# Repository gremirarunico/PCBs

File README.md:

# PCBs
## Informazioni
Repository privato per backup & share di PCB realizzati con KiCAD

## KiCad version
7.0.8

## License
Very easy to understand:
All the Hardware in this repository is under CERN-OHL-S v2
All the Software is under GPLv3
All the documentation is under CC-BY-SA 4.0

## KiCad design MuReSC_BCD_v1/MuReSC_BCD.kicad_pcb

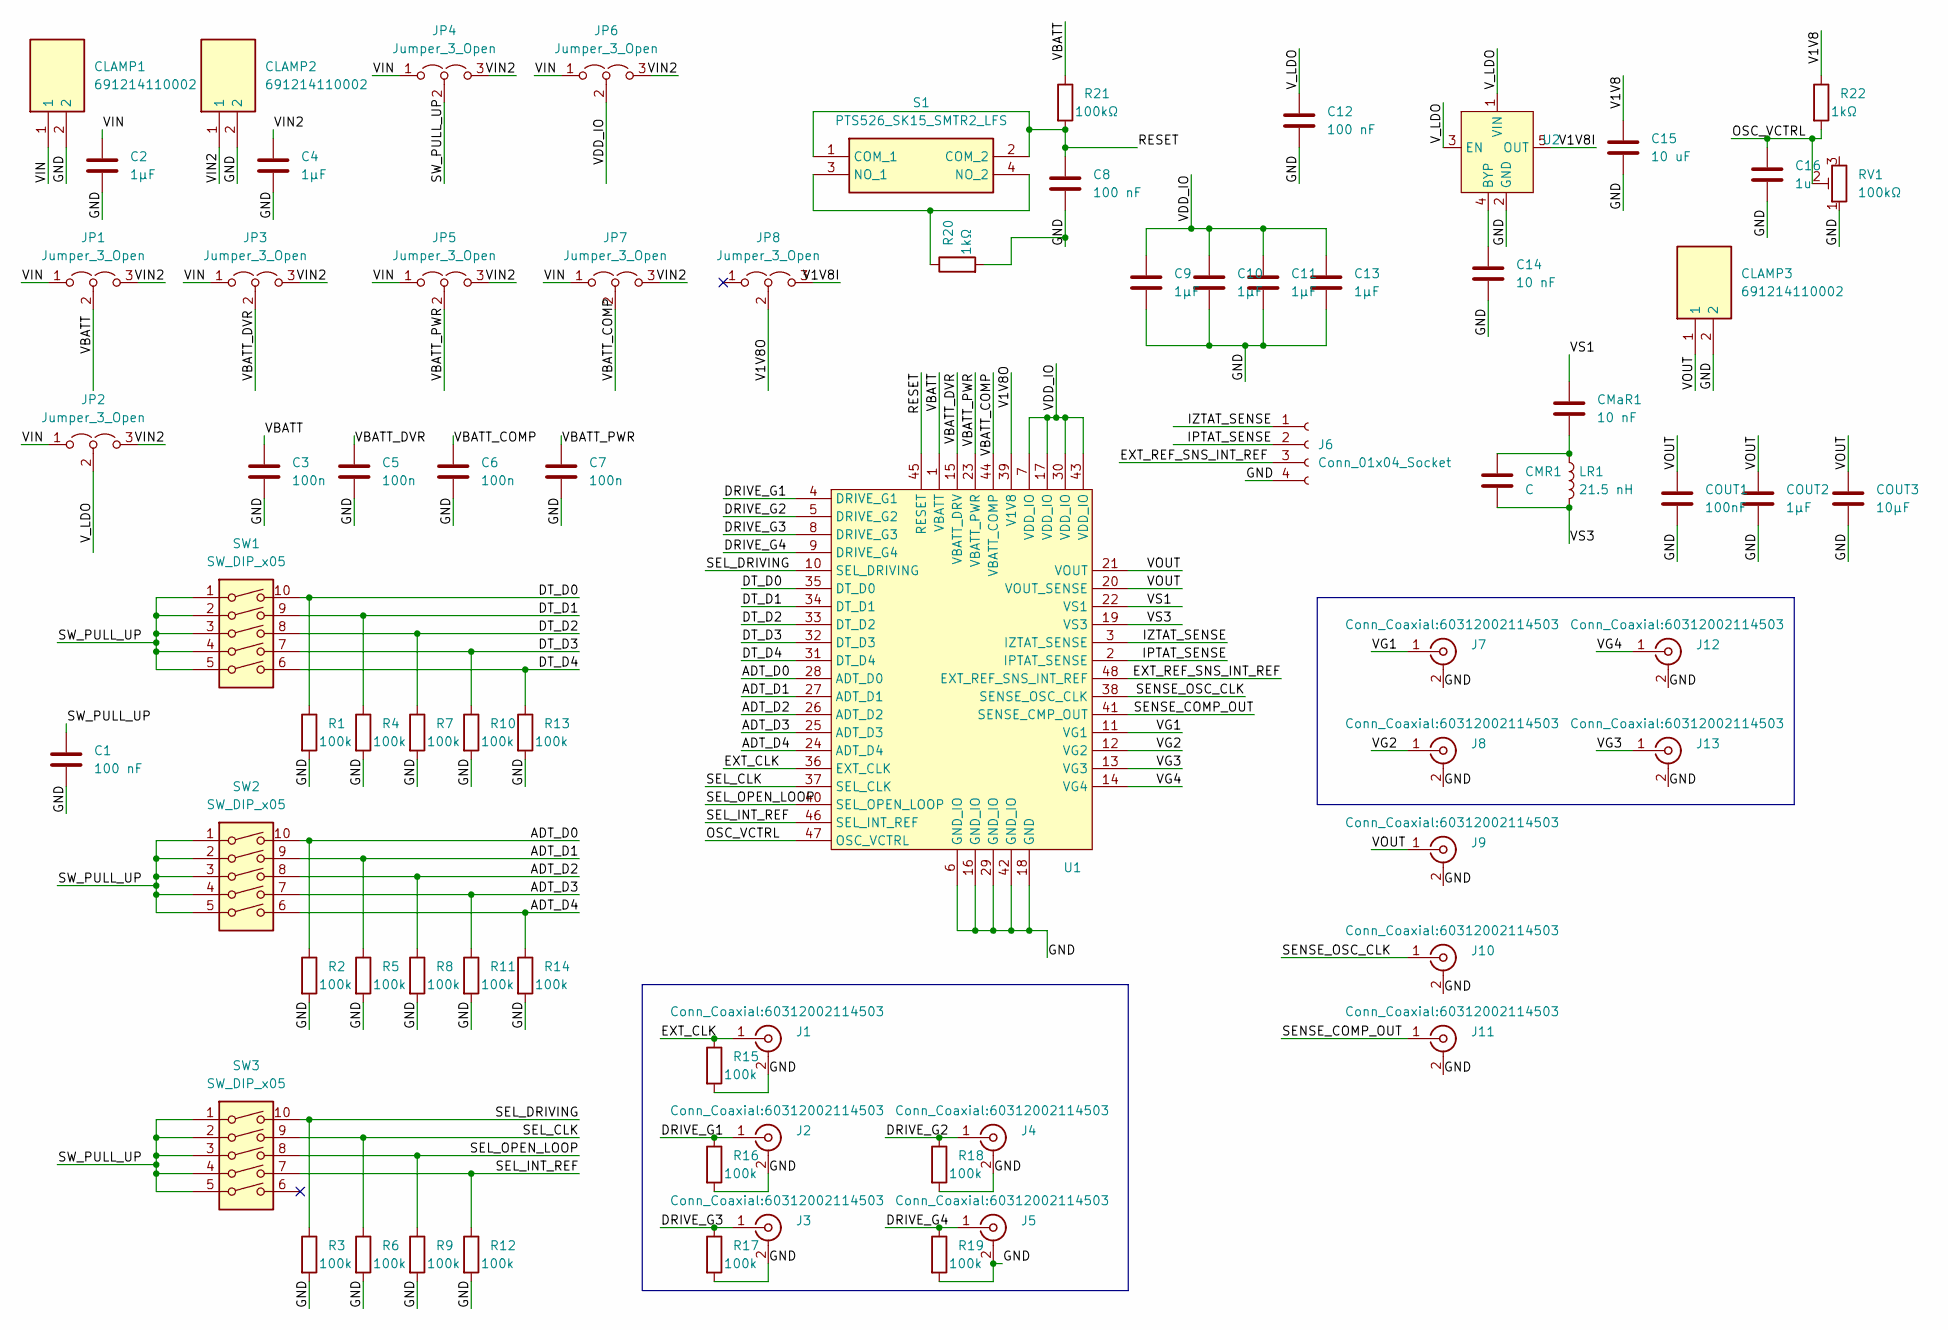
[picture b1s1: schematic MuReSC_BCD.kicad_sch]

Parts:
C1, C8, C12: 100 nF; C_0603_1608Metric_Pad1.08x0.95mm_HandSolder
C2, C4, C9, C10, C11, C13: 1µF; C_0603_1608Metric_Pad1.08x0.95mm_HandSolder
C3, C5, C6, C7: 100n; C_0603_1608Metric_Pad1.08x0.95mm_HandSolder
C14: 10 nF; C_0603_1608Metric_Pad1.08x0.95mm_HandSolder
C15: 10 uF; C_0603_1608Metric_Pad1.08x0.95mm_HandSolder
C16: 1u; C_0603_1608Metric_Pad1.08x0.95mm_HandSolder
CLAMP1, CLAMP2, CLAMP3: 691214110002; Mouser Part Number 710-691214110002
CMR1: C; C_0603_1608Metric_Pad1.08x0.95mm_HandSolder
CMaR1: 10 nF; C_0603_1608Metric_Pad1.08x0.95mm_HandSolder
COUT1: 100nF; C_0603_1608Metric_Pad1.08x0.95mm_HandSolder
COUT2: 1µF; C_0603_1608Metric_Pad1.08x0.95mm_HandSolder
COUT3: 10µF; C_0603_1608Metric_Pad1.08x0.95mm_HandSolder
J1, J2, J3, J4, J5, J7, J8, J9, J10, J11, J12, J13: Conn_Coaxial:60312002114503; SMA_Wurth_60312002114503_Vertical
J6: Conn_01x04_Socket; PinHeader_1x04_P2.54mm_Vertical
JP1, JP2, JP3, JP4, JP5, JP6, JP7, JP8: Jumper_3_Open; PinHeader_1x03_P2.54mm_Vertical
LR1: 21.5 nH; Coilcraft-Square-Air-Core-Inductors-all
R1, R2, R3, R4, R5, R6, R7, R8, R9, R10, R11, R12, R13, R14, R15, R16, R17, R18, R19: 100k; R_0603_1608Metric_Pad0.98x0.95mm_HandSolder
R20, R22: 1kΩ; R_0603_1608Metric_Pad0.98x0.95mm_HandSolder
R21: 100kΩ; R_0603_1608Metric_Pad0.98x0.95mm_HandSolder
RV1: 100kΩ; TS63X-VISHAY
S1: PTS526_SK15_SMTR2_LFS; PTS526SK15SMTR2LFS; Mouser Part Number 611-PTS526SK15SMR2L
SW1, SW2, SW3: SW_DIP_x05; DIP-10_W10.16mm_LongPads
U1: TQFP-48_7x7mm_P0.5mm
U2: SOT-23-5_HandSoldering

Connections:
/ADT_D0: R2.1, SW2.10, U1.28 (ADT_D0)
/ADT_D1: R5.1, SW2.9, U1.27 (ADT_D1)
/ADT_D2: R8.1, SW2.8, U1.26 (ADT_D2)
/ADT_D3: R11.1, SW2.7, U1.25 (ADT_D3)
/ADT_D4: R14.1, SW2.6, U1.24 (ADT_D4)
/DRIVE_G1: J2.1 (In), R16.1, U1.4 (DRIVE_G1)
/DRIVE_G2: J4.1 (In), R18.1, U1.5 (DRIVE_G2)
/DRIVE_G3: J3.1 (In), R17.1, U1.8 (DRIVE_G3)
/DRIVE_G4: J5.1 (In), R19.1, U1.9 (DRIVE_G4)
/DT_D0: R1.1, SW1.10, U1.35 (DT_D0)
/DT_D1: R4.1, SW1.9, U1.34 (DT_D1)
/DT_D2: R7.1, SW1.8, U1.33 (DT_D2)
/DT_D3: R10.1, SW1.7, U1.32 (DT_D3)
/DT_D4: R13.1, SW1.6, U1.31 (DT_D4)
/EXT_CLK: J1.1 (In), R15.1, U1.36 (EXT_CLK)
/EXT_REF_SNS_INT_REF: J6.3, U1.48 (EXT_REF_SNS_INT_REF)
/GND: C1.2, C2.2, C3.2, C4.2, C5.2, C6.2, C7.2, C8.2, C9.2, C10.2, C11.2, C12.2, C13.2, C14.2, C15.2, C16.2, CLAMP1.2, CLAMP2.2, CLAMP3.2, COUT1.2, COUT2.2, COUT3.2, J1.2 (Ext), J2.2 (Ext), J3.2 (Ext), J4.2 (Ext), J5.2 (Ext), J6.4, J7.2 (Ext), J8.2 (Ext), J9.2 (Ext), J10.2 (Ext), J11.2 (Ext), J12.2 (Ext), J13.2 (Ext), R1.2, R2.2, R3.2, R4.2, R5.2, R6.2, R7.2, R8.2, R9.2, R10.2, R11.2, R12.2, R13.2, R14.2, R15.2, R16.2, R17.2, R18.2, R19.2, R20.2, RV1.1, U1.6 (GND_IO), U1.16 (GND_IO), U1.18 (GND), U1.29 (GND_IO), U1.42 (GND_IO), U2.2 (GND)
/IPTAT_SENSE: J6.2, U1.2 (IPTAT_SENSE)
/IZTAT_SENSE: J6.1, U1.3 (IZTAT_SENSE)
/OSC_VCTRL: C16.1, R22.2, RV1.2, U1.47 (OSC_VCTRL)
/RESET: C8.1, R21.2, S1.1 (COM_1), S1.2 (COM_2), U1.45 (RESET)
/SEL_CLK: R6.1, SW3.9, U1.37 (SEL_CLK)
/SEL_DRIVING: R3.1, SW3.10, U1.10 (SEL_DRIVING)
/SEL_INT_REF: R12.1, SW3.7, U1.46 (SEL_INT_REF)
/SEL_OPEN_LOOP: R9.1, SW3.8, U1.40 (SEL_OPEN_LOOP)
/SENSE_COMP_OUT: J11.1 (In), U1.41 (SENSE_CMP_OUT)
/SENSE_OSC_CLK: J10.1 (In), U1.38 (SENSE_OSC_CLK)
/SW_PULL_UP: C1.1, JP4.2 (C), SW1.1, SW1.2, SW1.3, SW1.4, SW1.5, SW2.1, SW2.2, SW2.3, SW2.4, SW2.5, SW3.1, SW3.2, SW3.3, SW3.4, SW3.5
/V1V8: C15.1, R22.1
/V1V8I: JP8.3 (B), U2.5 (OUT)
/V1V8O: JP8.2 (C), U1.39 (V1V8)
/VBATT: C3.1, JP1.2 (C), R21.1, U1.1 (VBATT)
/VBATT_COMP: C6.1, JP7.2 (C), U1.44 (VBATT_COMP)
/VBATT_DVR: C5.1, JP3.2 (C), U1.15 (VBATT_DRV)
/VBATT_PWR: C7.1, JP5.2 (C), U1.23 (VBATT_PWR)
/VDD_IO: C9.1, C10.1, C11.1, C13.1, JP6.2 (C), U1.7 (VDD_IO), U1.17 (VDD_IO), U1.30 (VDD_IO), U1.43 (VDD_IO)
/VG1: J7.1 (In), U1.11 (VG1)
/VG2: J8.1 (In), U1.12 (VG2)
/VG3: J13.1 (In), U1.13 (VG3)
/VG4: J12.1 (In), U1.14 (VG4)
/VIN: C2.1, CLAMP1.1, JP1.1 (A), JP2.1 (A), JP3.1 (A), JP4.1 (A), JP5.1 (A), JP6.1 (A), JP7.1 (A)
/VIN2: C4.1, CLAMP2.1, JP1.3 (B), JP2.3 (B), JP3.3 (B), JP4.3 (B), JP5.3 (B), JP6.3 (B), JP7.3 (B)
/VOUT: CLAMP3.1, COUT1.1, COUT2.1, COUT3.1, J9.1 (In), U1.20 (VOUT_SENSE), U1.21 (VOUT)
/VS1: CMaR1.1, U1.22 (VS1)
/VS3: CMR1.2, LR1.2, U1.19 (VS3)
/V_LDO: C12.1, JP2.2 (C), U2.1 (VIN), U2.3 (EN)
unnamed: CMR1.1, CMaR1.2, LR1.1
unnamed: R20.1, S1.3 (NO_1), S1.4 (NO_2)
unnamed: C14.1, U2.4 (BYP)

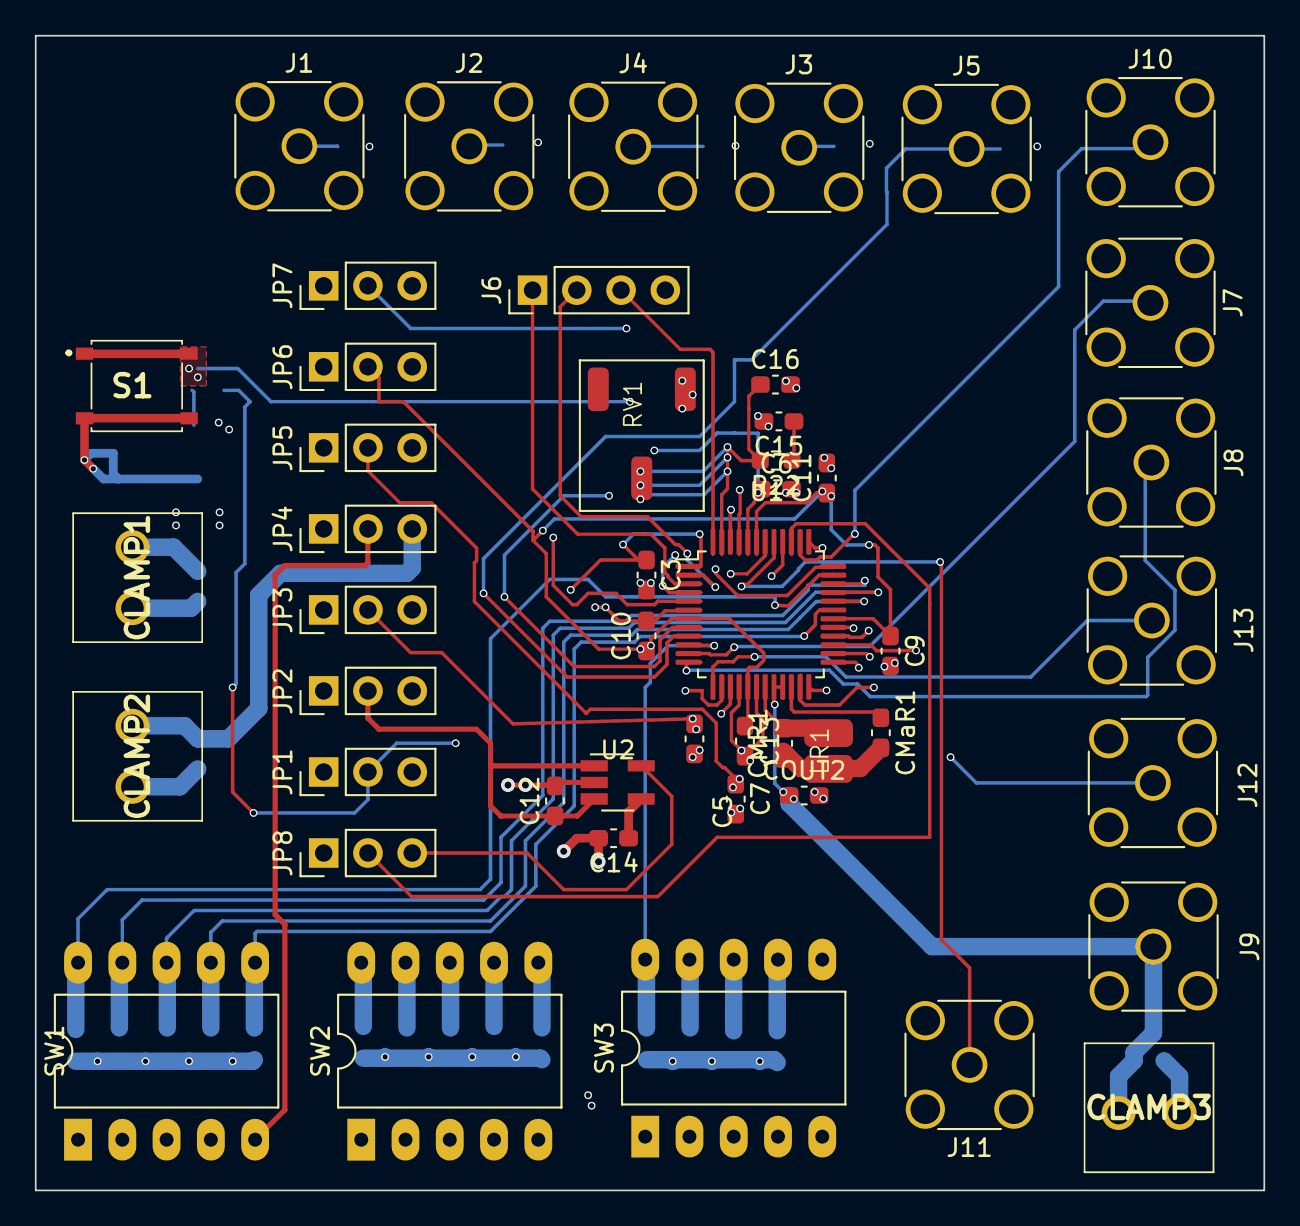
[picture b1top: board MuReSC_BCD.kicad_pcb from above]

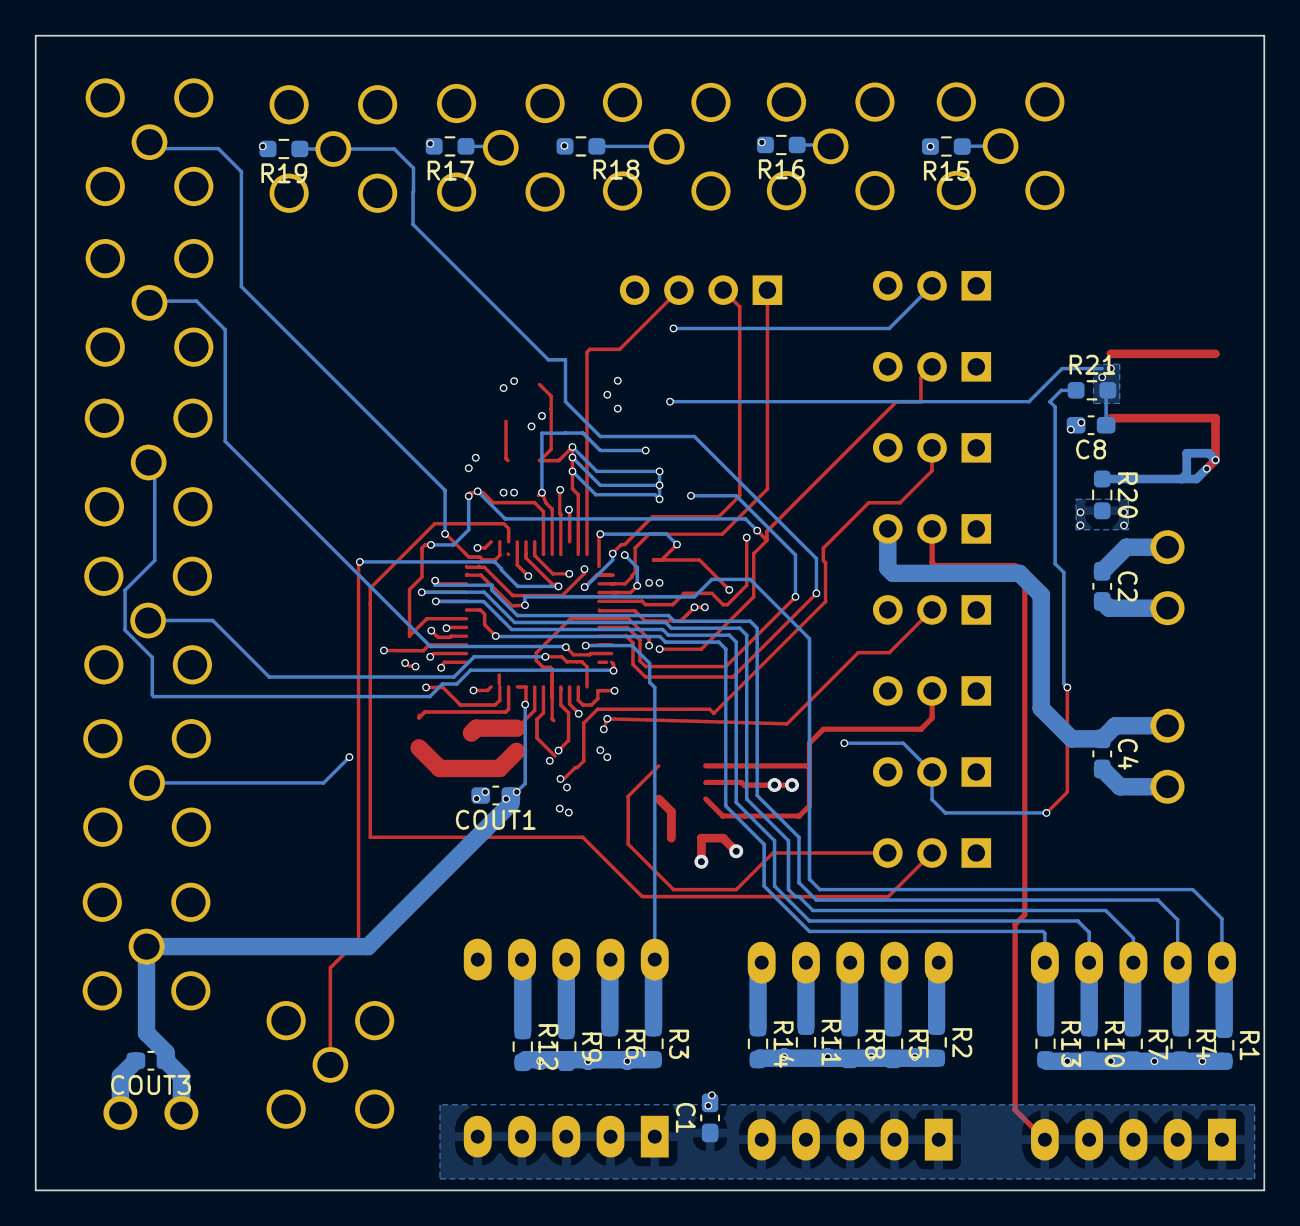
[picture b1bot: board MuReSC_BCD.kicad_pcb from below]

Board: 4 copper layers, 70.5 x 66.3 mm, 75 parts (27 on the bottom side), 49 nets.

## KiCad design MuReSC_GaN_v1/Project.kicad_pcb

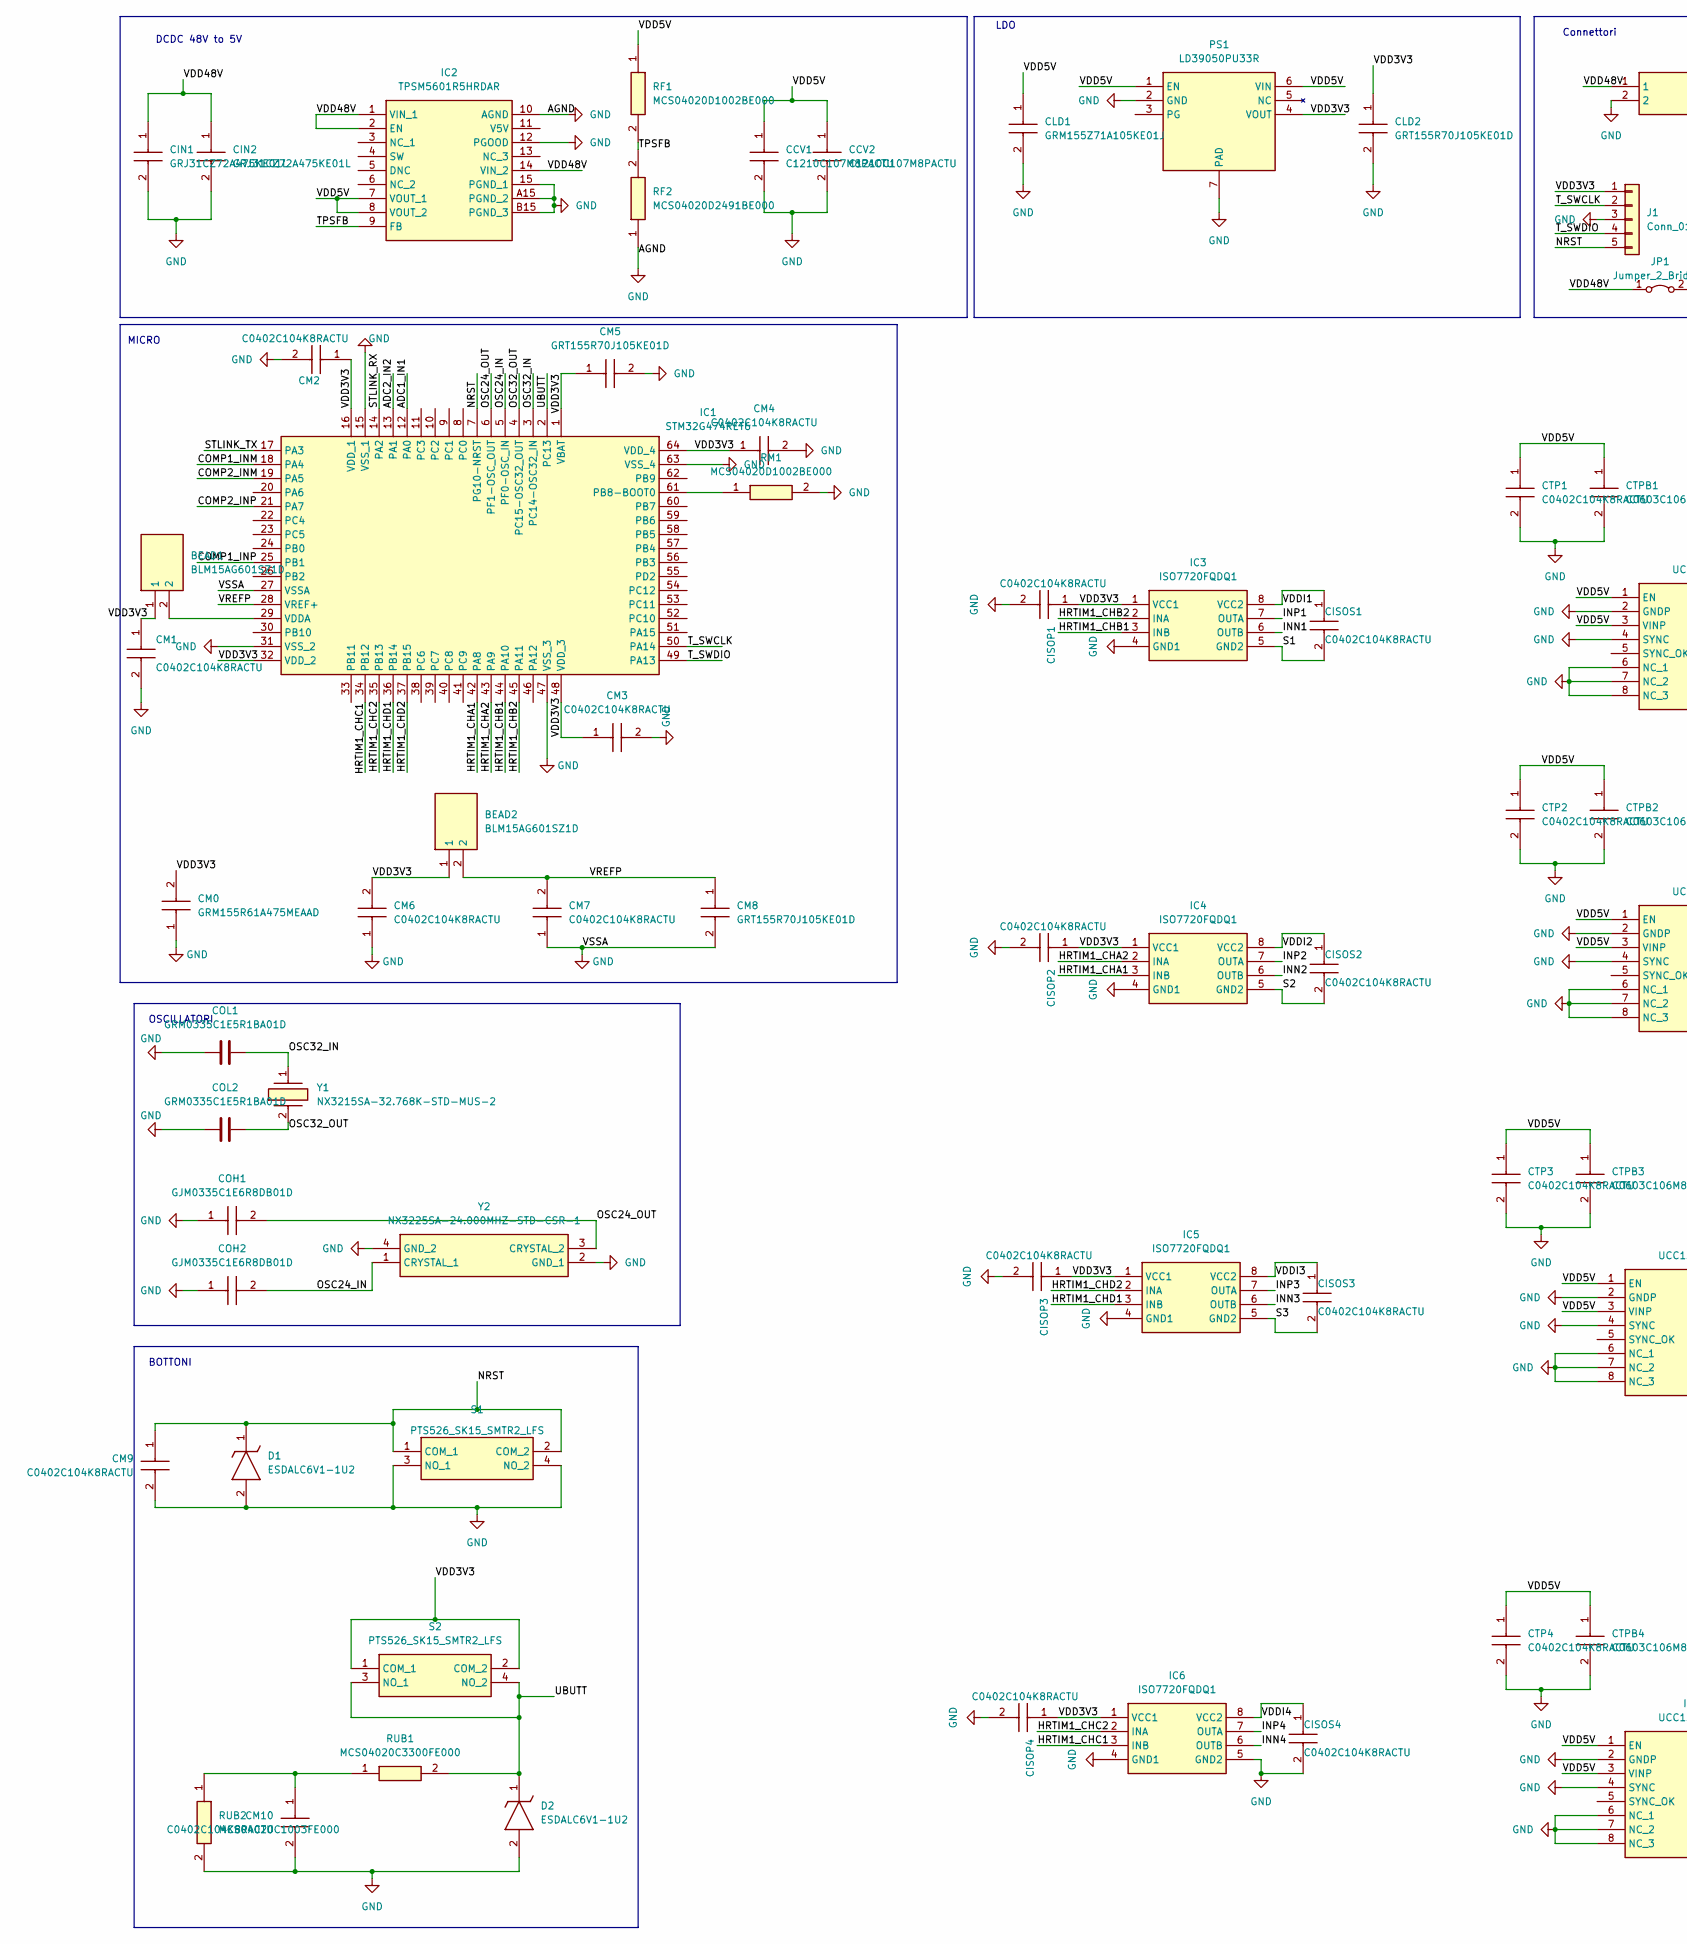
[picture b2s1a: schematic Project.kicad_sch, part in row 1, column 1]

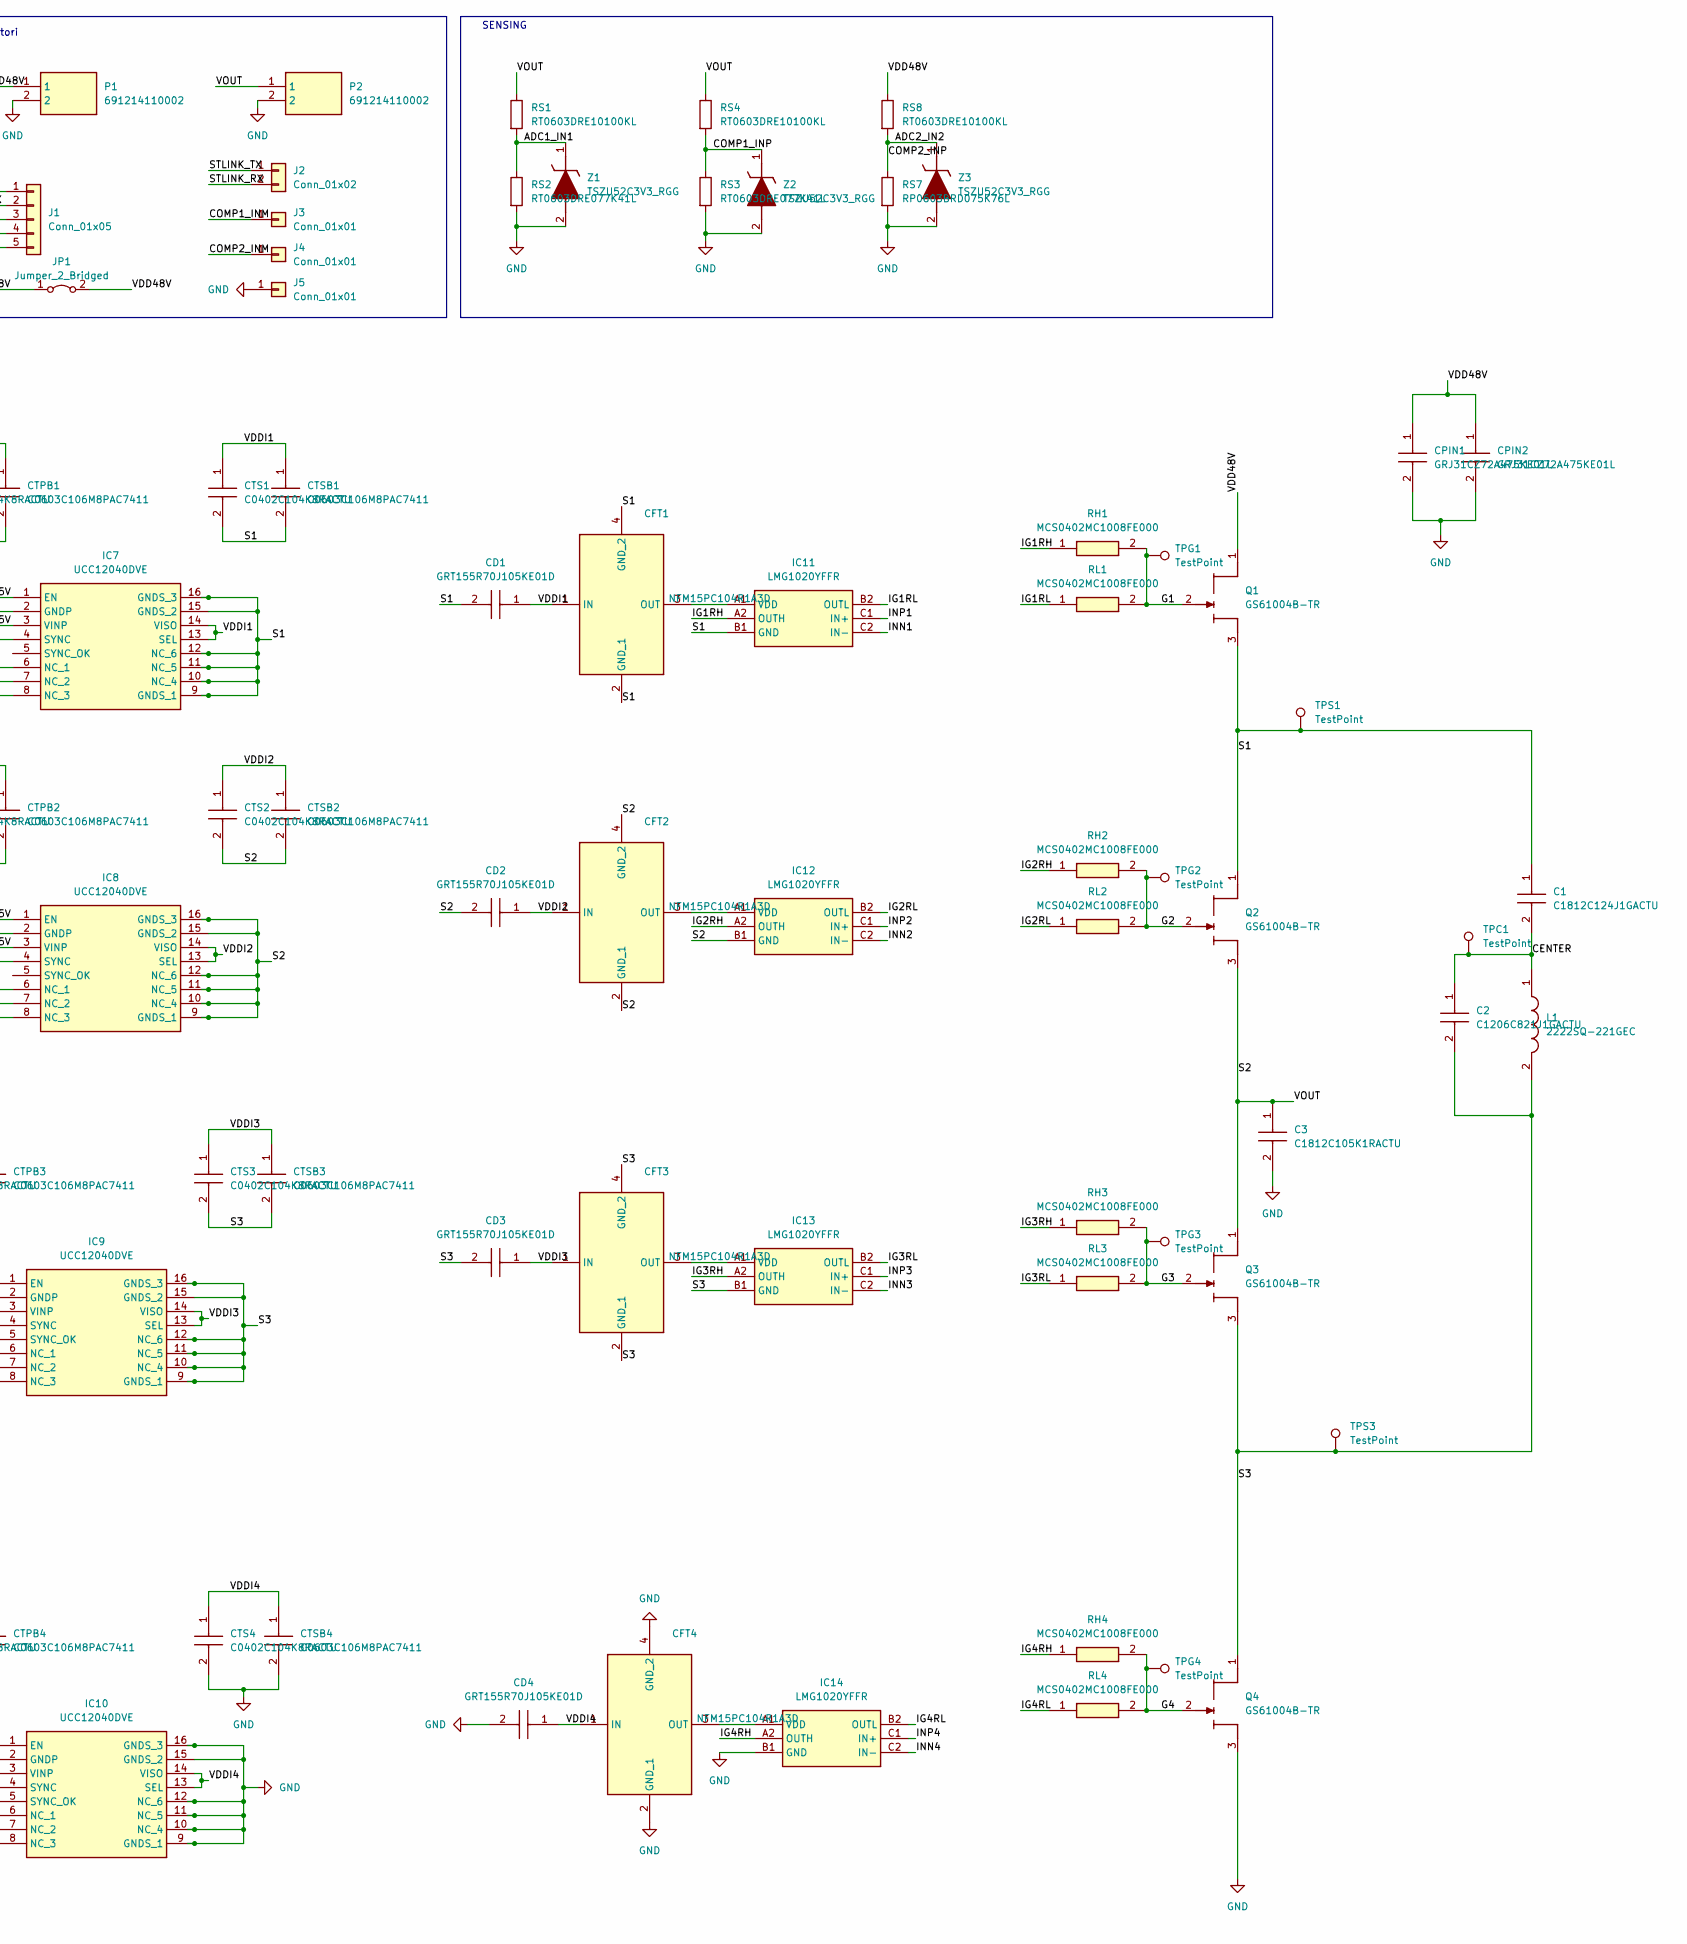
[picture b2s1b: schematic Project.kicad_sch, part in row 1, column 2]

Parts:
BEAD1, BEAD2: BLM15AG601SZ1D; NFZ15SG152SN10B; Mouser Part Number 81-BLM15AG601SZ1D
C1: C1812C124J1GACTU; C1812; Mouser Part Number 80-C1812C124J1G
C2: C1206C821J1GACTU; C1206; Manufacturer_Part_Number C1206C821J1GACTU
C3: C1812C105K1RACTU; C1812; Mouser Part Number 80-C1812C105K1R
CCV1, CCV2: C1210C107M8PACTU; C1210; Mouser Part Number 80-C1210C107M8P
CD1, CD2, CD3, CD4: GRT155R70J105KE01D; CAPC1005X55N; Mouser Part Number 81-GRT155R70J105KE1D
CFT1, CFT2, CFT3, CFT4: NFM15PC104R1A3D; NFM15CC222D1A3D; Mouser Part Number 81-NFM15PC104R1A3D
CIN1, CIN2: GRJ31CZ72A475KE01L; CAPC3216X190N; Mouser Part Number 81-GRJ31CZ72A475KE1L
CISOP1, CISOP2, CISOP3, CISOP4: C0402C104K8RACTU; CAPC1005X55N; Mouser Part Number 81-GRT155R70J105KE1D
CISOS1, CISOS2, CISOS3, CISOS4: C0402C104K8RACTU; CAPC1005X55N; Mouser Part Number 81-GRT155R70J105KE1D
CLD1: GRM155Z71A105KE01J; CAPC1005X55N; Mouser Part Number 81-GRM155Z71A105KE1J
CLD2: GRT155R70J105KE01D; CAPC1005X55N; Mouser Part Number 81-GRT155R70J105KE1D
CM0: GRM155R61A475MEAAD; CAPC1005X55N; Mouser Part Number 81-GRM155R61A475MEAD
CM1, CM2, CM3, CM4, CM6, CM7, CM9, CM10: C0402C104K8RACTU; CAPC1005X55N; Mouser Part Number 80-C0402C104K8R7867
CM5, CM8: GRT155R70J105KE01D; CAPC1005X55N; Mouser Part Number 81-GRT155R70J105KE1D
COH1, COH2: GJM0335C1E6R8DB01D; CAPC0603X33N; Mouser Part Number 81-GJM0335C1E6R8DB1D
COL1, COL2: GRM0335C1E5R1BA01D; CAPC0603X33N
CPIN1, CPIN2: GRJ31CZ72A475KE01L; CAPC3216X190N; Mouser Part Number 81-GRJ31CZ72A475KE1L
CTP1, CTP2, CTP3, CTP4: C0402C104K8RACTU; CAPC1005X55N; Mouser Part Number 80-C0402C104K8R7867
CTPB1, CTPB2, CTPB3, CTPB4: C0603C106M8PAC7411; C0603; Mouser Part Number 80-C0603C106M8PLR
CTS1, CTS2, CTS3, CTS4: C0402C104K8RACTU; CAPC1005X55N; Mouser Part Number 80-C0402C104K8R7867
CTSB1, CTSB2, CTSB3, CTSB4: C0603C106M8PAC7411; C0603; Mouser Part Number 80-C0603C106M8PLR
D1, D2: ESDALC6V1-1U2; ESDALC6V11U2; Mouser Part Number 511-ESDALC6V1-1U2
IC1: STM32G474RET6; QFP50P1200X1200X160-64N; Mouser Part Number 511-STM32G474RET6
IC2: TPSM5601R5HRDAR; Mouser Part Number 595-TPSM5601R5HRDAR
IC3, IC4, IC5, IC6: ISO7720FQDQ1; SOIC127P600X175-8N; Mouser Part Number 595-ISO7720FQDQ1
IC7, IC8, IC9, IC10: UCC12040DVE; SOIC127P1030X265-16N; Mouser Part Number 595-UCC12040DVE
IC11, IC12, IC13, IC14: LMG1020YFFR; BGA6C40P2X3_86X126X62; Mouser Part Number 595-LMG1020YFFR
J1: Conn_01x05; PinHeader_1x05_P2.54mm_Horizontal
J2: Conn_01x02; PinHeader_1x02_P2.54mm_Horizontal
J3, J4, J5: Conn_01x01; PinHeader_1x01_P2.54mm_Vertical
JP1: Jumper_2_Bridged; PinHeader_1x02_P2.54mm_Horizontal
L1: 2222SQ-221GEC; 2222SQ221GEC; Mouser Part Number 994-2222SQ-221GEC
P1, P2: 691214110002; Mouser Part Number 710-691214110002
PS1: LD39050PU33R; SON95P300X300X100-7N-D; Mouser Part Number 511-LD39050PU33R
Q1, Q2, Q3, Q4: GS61004B-TR; GS61004BTR; Mouser Part Number 499-GS61004B-TR
RF1: MCS04020D1002BE000; RESC1005X37N; Mouser Part Number 594-MCS04020D1002BE0
RF2: MCS04020D2491BE000; RESC1005X37N; Mouser Part Number 594-MCS04020D2491BE0
RH1, RH2, RH3, RH4: MCS0402MC1008FE000; RESC1005X37N; Mouser Part Number 594-MCS0402MC1008FE0
RL1, RL2, RL3, RL4: MCS0402MC1008FE000; RESC1005X37N; Mouser Part Number 594-MCS0402MC1008FE0
RM1: MCS04020D1002BE000; RESC1005X37N; Mouser Part Number 594-MCS04020D1002BE0
RS1, RS4, RS8: RT0603DRE10100KL; R_0603_1608Metric_Pad0.98x0.95mm_HandSolder
RS2, RS3: RT0603DRE077K41L; R_0603_1608Metric_Pad0.98x0.95mm_HandSolder
RS7: RP0603BRD075K76L; R_0603_1608Metric_Pad0.98x0.95mm_HandSolder
RUB1: MCS04020C3300FE000; RESC1005X37N; Mouser Part Number 594-MCS04020C3300FE0
RUB2: MCS04020C1003FE000; RESC1005X37N; Mouser Part Number 594-MCS04020C1003FE0
S1, S2: PTS526_SK15_SMTR2_LFS; PTS526SK15SMTR2LFS; Mouser Part Number 611-PTS526SK15SMR2L
TPC1: TestPoint; TestPoint_Pad_1.0x1.0mm
TPG1, TPG2, TPG3, TPG4: TestPoint; TestPoint_Pad_1.0x1.0mm
TPS1, TPS3: TestPoint; TestPoint_Pad_1.0x1.0mm
Y1: NX3215SA-32.768K-STD-MUS-2; NX3215SA32768KSTDMUS2; Manufacturer_Part_Number NX3215SA-32.768K-STD-MUS-2
Y2: NX3225SA-24.000MHZ-STD-CSR-1; NX3225SA24000MHZSTDCSR1; Mouser Part Number 344-NX3225SA24MCSR1
Z1, Z2, Z3: TSZU52C3V3_RGG; TSZU52C3V3RGG; Mouser Part Number 821-TSZU52C3V3RGG

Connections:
/ADC1_IN1: IC1.12 (PA0), RS1.2, RS2.1, Z1.1 (K)
/ADC2_IN2: IC1.13 (PA1), IC1.21 (PA7), RS7.1, RS8.2, Z3.1 (K)
/CENTER: C1.2, C2.1, L1.1, TPC1.1
/COMP1_INM: IC1.18 (PA4), J3.1
/COMP1_INP: IC1.25 (PB1), RS3.1, RS4.2, Z2.1 (K)
/COMP2_INM: IC1.19 (PA5), J4.1
/G1: Q1.2 (G), RH1.2, RL1.2, TPG1.1
/G2: Q2.2 (G), RH2.2, RL2.2, TPG2.1
/G3: Q3.2 (G), RH3.2, RL3.2, TPG3.1
/G4: Q4.2 (G), RH4.2, RL4.2, TPG4.1
/HRTIM1_CHA1: IC1.42 (PA8), IC4.3 (INB)
/HRTIM1_CHA2: IC1.43 (PA9), IC4.2 (INA)
/HRTIM1_CHB1: IC1.44 (PA10), IC3.3 (INB)
/HRTIM1_CHB2: IC1.45 (PA11), IC3.2 (INA)
/HRTIM1_CHC1: IC1.34 (PB12), IC6.3 (INB)
/HRTIM1_CHC2: IC1.35 (PB13), IC6.2 (INA)
/HRTIM1_CHD1: IC1.36 (PB14), IC5.3 (INB)
/HRTIM1_CHD2: IC1.37 (PB15), IC5.2 (INA)
/IG1RH: IC11.A2 (OUTH), RH1.1
/IG1RL: IC11.B2 (OUTL), RL1.1
/IG2RH: IC12.A2 (OUTH), RH2.1
/IG2RL: IC12.B2 (OUTL), RL2.1
/IG3RH: IC13.A2 (OUTH), RH3.1
/IG3RL: IC13.B2 (OUTL), RL3.1
/IG4RH: IC14.A2 (OUTH), RH4.1
/IG4RL: IC14.B2 (OUTL), RL4.1
/INN1: IC3.6 (OUTB), IC11.C2 (IN-)
/INN2: IC4.6 (OUTB), IC12.C2 (IN-)
/INN3: IC5.6 (OUTB), IC13.C2 (IN-)
/INN4: IC6.6 (OUTB), IC14.C2 (IN-)
/INP1: IC3.7 (OUTA), IC11.C1 (IN+)
/INP2: IC4.7 (OUTA), IC12.C1 (IN+)
/INP3: IC5.7 (OUTA), IC13.C1 (IN+)
/INP4: IC6.7 (OUTA), IC14.C1 (IN+)
/NRST: CM9.1, D1.1 (K), IC1.7 (PG10-NRST), J1.5, S1.1 (COM_1), S1.2 (COM_2)
/OSC24_IN: COH2.2, IC1.5 (PF0-OSC_IN), Y2.1 (CRYSTAL_1)
/OSC24_OUT: COH1.2, IC1.6 (PF1-OSC_OUT), Y2.3 (CRYSTAL_2)
/OSC32_IN: COL1.2, IC1.3 (PC14-OSC32_IN), Y1.1
/OSC32_OUT: COL2.2, IC1.4 (PC15-OSC32_OUT), Y1.2
/S1: C1.1, CD1.2, CFT1.2 (GND_1), CFT1.4 (GND_2), CISOS1.2, CTS1.2, CTSB1.2, IC3.5 (GND2), IC7.9 (GNDS_1), IC7.10 (NC_4), IC7.11 (NC_5), IC7.12 (NC_6), IC7.15 (GNDS_2), IC7.16 (GNDS_3), IC11.B1 (GND), Q1.3 (S), Q2.1 (D), TPS1.1
/S2: C3.1, CD2.2, CFT2.2 (GND_1), CFT2.4 (GND_2), CISOS2.2, CTS2.2, CTSB2.2, IC4.5 (GND2), IC8.9 (GNDS_1), IC8.10 (NC_4), IC8.11 (NC_5), IC8.12 (NC_6), IC8.15 (GNDS_2), IC8.16 (GNDS_3), IC12.B1 (GND), P2.1, Q2.3 (S), Q3.1 (D), RS1.1, RS4.1
/S3: C2.2, CD3.2, CFT3.2 (GND_1), CFT3.4 (GND_2), CISOS3.2, CTS3.2, CTSB3.2, IC5.5 (GND2), IC9.9 (GNDS_1), IC9.10 (NC_4), IC9.11 (NC_5), IC9.12 (NC_6), IC9.15 (GNDS_2), IC9.16 (GNDS_3), IC13.B1 (GND), L1.2, Q3.3 (S), Q4.1 (D), TPS3.1
/STLINK_RX: IC1.14 (PA2), J2.2
/STLINK_TX: IC1.17 (PA3), J2.1
/TPSFB: IC2.9 (FB), RF1.2, RF2.2
/T_SWCLK: IC1.50 (PA14), J1.2
/T_SWDIO: IC1.49 (PA13), J1.4
/UBUTT: D2.1 (K), IC1.2 (PC13), RUB1.2, S2.3 (NO_1), S2.4 (NO_2)
/VDD3V3: BEAD1.1, BEAD2.1, CISOP1.1, CISOP2.1, CISOP3.1, CISOP4.1, CLD2.1, CM0.2, CM1.1, CM2.1, CM3.1, CM4.1, CM5.1, CM6.2, IC1.1 (VBAT), IC1.16 (VDD_1), IC1.32 (VDD_2), IC1.48 (VDD_3), IC1.64 (VDD_4), IC3.1 (VCC1), IC4.1 (VCC1), IC5.1 (VCC1), IC6.1 (VCC1), J1.1, PS1.4 (VOUT), S2.1 (COM_1), S2.2 (COM_2)
/VDD5V: CCV1.1, CCV2.1, CLD1.1, CTP1.1, CTP2.1, CTP3.1, CTP4.1, CTPB1.1, CTPB2.1, CTPB3.1, CTPB4.1, IC2.7 (VOUT_1), IC2.8 (VOUT_2), IC7.1 (EN), IC7.3 (VINP), IC8.1 (EN), IC8.3 (VINP), IC9.1 (EN), IC9.3 (VINP), IC10.1 (EN), IC10.3 (VINP), PS1.1 (EN), PS1.6 (VIN), RF1.1
/VDD48V: CIN1.1, CIN2.1, CPIN1.1, CPIN2.1, IC2.1 (VIN_1), IC2.2 (EN), IC2.14 (VIN_2), JP1.1 (A), JP1.2 (B), P1.1, Q1.1 (D), RS8.1
/VDDI1: CD1.1, CFT1.1 (IN), CISOS1.1, CTS1.1, CTSB1.1, IC3.8 (VCC2), IC7.13 (SEL), IC7.14 (VISO)
/VDDI2: CD2.1, CFT2.1 (IN), CISOS2.1, CTS2.1, CTSB2.1, IC4.8 (VCC2), IC8.13 (SEL), IC8.14 (VISO)
/VDDI3: CD3.1, CFT3.1 (IN), CISOS3.1, CTS3.1, CTSB3.1, IC5.8 (VCC2), IC9.13 (SEL), IC9.14 (VISO)
/VDDI4: CD4.1, CFT4.1 (IN), CISOS4.1, CTS4.1, CTSB4.1, IC6.8 (VCC2), IC10.13 (SEL), IC10.14 (VISO)
/VREFP: BEAD2.2, CM7.2, CM8.1, IC1.28 (VREF+)
GND: C3.2, CCV1.2, CCV2.2, CD4.2, CFT4.2 (GND_1), CFT4.4 (GND_2), CIN1.2, CIN2.2, CISOP1.2, CISOP2.2, CISOP3.2, CISOP4.2, CISOS4.2, CLD1.2, CLD2.2, CM0.1, CM1.2, CM2.2, CM3.2, CM4.2, CM5.2, CM6.1, CM7.1, CM8.2, CM9.2, CM10.2, COH1.1, COH2.1, COL1.1, COL2.1, CPIN1.2, CPIN2.2, CTP1.2, CTP2.2, CTP3.2, CTP4.2, CTPB1.2, CTPB2.2, CTPB3.2, CTPB4.2, CTS4.2, CTSB4.2, D1.2 (A), D2.2 (A), IC1.15 (VSS_1), IC1.27 (VSSA), IC1.31 (VSS_2), IC1.47 (VSS_3), IC1.63 (VSS_4), IC2.10 (AGND), IC2.12 (PGOOD), IC2.15 (PGND_1), IC2.A15 (PGND_2), IC2.B15 (PGND_3), IC3.4 (GND1), IC4.4 (GND1), IC5.4 (GND1), IC6.4 (GND1), IC6.5 (GND2), IC7.2 (GNDP), IC7.4 (SYNC), IC7.6 (NC_1), IC7.7 (NC_2), IC7.8 (NC_3), IC8.2 (GNDP), IC8.4 (SYNC), IC8.6 (NC_1), IC8.7 (NC_2), IC8.8 (NC_3), IC9.2 (GNDP), IC9.4 (SYNC), IC9.6 (NC_1), IC9.7 (NC_2), IC9.8 (NC_3), IC10.2 (GNDP), IC10.4 (SYNC), IC10.6 (NC_1), IC10.7 (NC_2), IC10.8 (NC_3), IC10.9 (GNDS_1), IC10.10 (NC_4), IC10.11 (NC_5), IC10.12 (NC_6), IC10.15 (GNDS_2), IC10.16 (GNDS_3), IC14.B1 (GND), J1.3, J5.1, P1.2, P2.2, PS1.2 (GND), PS1.7 (PAD), Q4.3 (S), RF2.1, RM1.2, RS2.2, RS3.2, RS7.2, RUB2.2, S1.3 (NO_1), S1.4 (NO_2), Y2.2 (GND_1), Y2.4 (GND_2), Z1.2 (A), Z2.2 (A), Z3.2 (A)
unnamed: CFT1.3 (OUT), IC11.A1 (VDD)
unnamed: CFT2.3 (OUT), IC12.A1 (VDD)
unnamed: CFT3.3 (OUT), IC13.A1 (VDD)
unnamed: CFT4.3 (OUT), IC14.A1 (VDD)
unnamed: CM10.1, RUB1.1, RUB2.1
unnamed: IC1.61 (PB8-BOOT0), RM1.1
unnamed: BEAD1.2, IC1.29 (VDDA)

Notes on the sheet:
BOTTONI
MICRO
Connettori
OSCILLATORI
DCDC 48V to 5V
SENSING
LDO

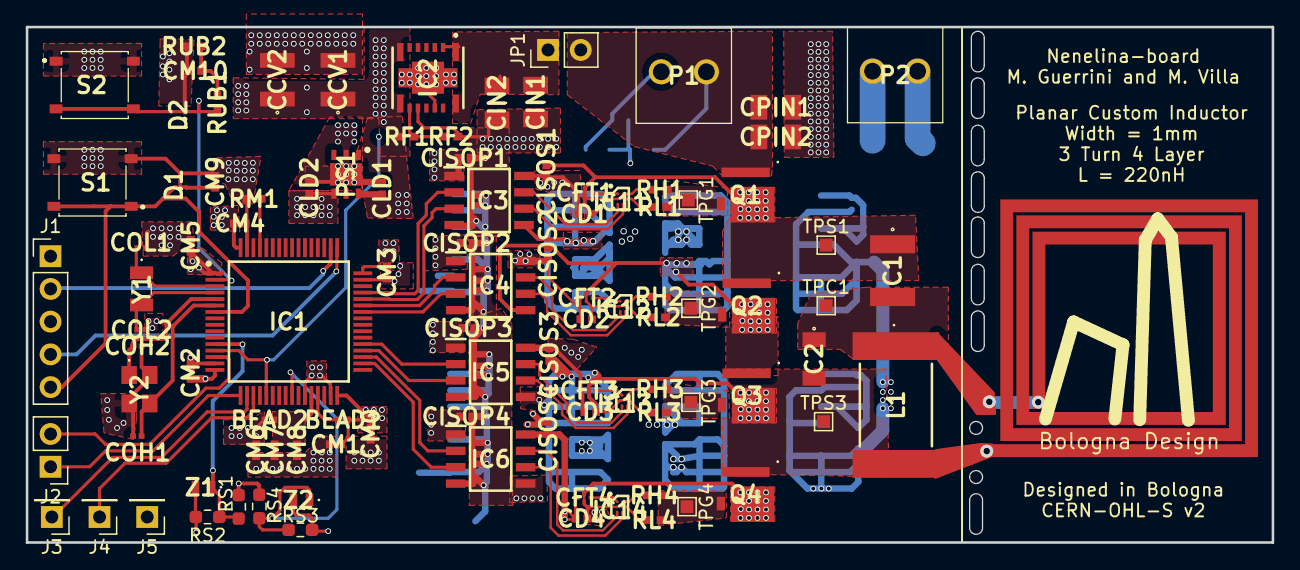
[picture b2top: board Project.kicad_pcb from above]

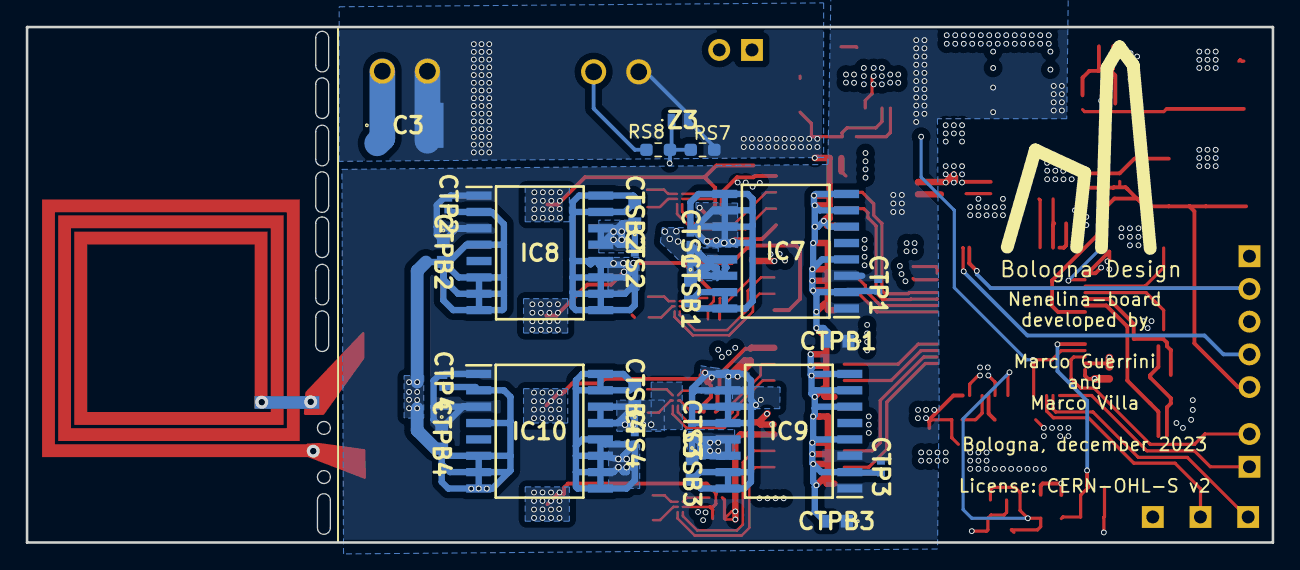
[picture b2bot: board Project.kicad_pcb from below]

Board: 4 copper layers, 96.7 x 40.0 mm, 123 parts (24 on the bottom side), 64 nets.

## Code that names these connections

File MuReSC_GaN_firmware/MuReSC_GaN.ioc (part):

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Mcu.Name=STM32G474R(B-C-E)Tx
Mcu.Package=LQFP64
Mcu.UserName=STM32G474RETx
PA10.GPIOParameters=GPIO_PuPd
PA10.GPIO_PuPd=GPIO_PULLUP
PA10.Mode=Output_TB1TB2
PA10.Signal=HRTIM1_CHB1
PA11.GPIOParameters=GPIO_PuPd
PA11.GPIO_PuPd=GPIO_PULLDOWN
PA11.Mode=Output_TB1TB2
PA11.Signal=HRTIM1_CHB2
PA13.GPIOParameters=GPIO_Label
PA13.GPIO_Label=T_SWDIO
PA13.Mode=Serial_Wire
PA13.Signal=SYS_JTMS-SWDIO
PA14.GPIOParameters=GPIO_Label
PA14.GPIO_Label=T_SWCLK
PA14.Mode=Serial_Wire
PA14.Signal=SYS_JTCK-SWCLK
PA2.GPIOParameters=GPIO_Label
PA2.GPIO_Label=LPUART1_TX [STLINKV3E_VCP_RX]
PA2.Mode=Asynchronous
PA2.Signal=LPUART1_TX
PA3.GPIOParameters=GPIO_Label
PA3.GPIO_Label=LPUART1_RX [STLINKV3E_VCP_TX]
PA3.Mode=Asynchronous
PA3.Signal=LPUART1_RX
PA4.Signal=COMP_DAC11_group
PA8.GPIOParameters=GPIO_PuPd
PA8.GPIO_PuPd=GPIO_PULLUP
PA8.Mode=Output_TA1TA2
PA8.Signal=HRTIM1_CHA1
PA9.GPIOParameters=GPIO_PuPd
PA9.GPIO_PuPd=GPIO_PULLDOWN
PA9.Mode=Output_TA1TA2
PA9.Signal=HRTIM1_CHA2
PB1.Mode=INP
PB1.Signal=COMP1_INP
PB12.GPIOParameters=GPIO_PuPd
PB12.GPIO_PuPd=GPIO_PULLUP
PB12.Mode=Output_TC1TC2
PB12.Signal=HRTIM1_CHC1
PB13.GPIOParameters=GPIO_PuPd
PB13.GPIO_PuPd=GPIO_PULLDOWN
PB13.Mode=Output_TC1TC2
PB13.Signal=HRTIM1_CHC2
PB14.GPIOParameters=GPIO_PuPd
PB14.GPIO_PuPd=GPIO_PULLUP
PB14.Mode=Output_TD1TD2
PB14.Signal=HRTIM1_CHD1
PB15.GPIOParameters=GPIO_PuPd
PB15.GPIO_PuPd=GPIO_PULLDOWN
PB15.Mode=Output_TD1TD2
PB15.Signal=HRTIM1_CHD2
PC13.GPIOParameters=GPIO_Label
PC13.GPIO_Label=USER_BUTTON
PC13.Signal=GPIO_Input
PC14-OSC32_IN.Mode=LSE-External-Oscillator
PC14-OSC32_IN.Signal=RCC_OSC32_IN
PC15-OSC32_OUT.Mode=LSE-External-Oscillator
PC15-OSC32_OUT.Signal=RCC_OSC32_OUT
PF0-OSC_IN.Mode=HSE-External-Oscillator
PF0-OSC_IN.Signal=RCC_OSC_IN
PF1-OSC_OUT.Mode=HSE-External-Oscillator
PF1-OSC_OUT.Signal=RCC_OSC_OUT
RCC.HSE_VALUE=24000000
RCC.SYSCLKFreq_VALUE=170000000
RCC.SYSCLKSource=RCC_SYSCLKSOURCE_PLLCLK
board=NUCLEO-G474RE
boardIOC=true

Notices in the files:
MuReSC_GaN_v1/Project.kicad_pcb:
License: CERN-OHL-S v2
